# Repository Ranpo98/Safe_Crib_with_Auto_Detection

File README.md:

# Safe Crib With Auto Hazard-Detection

## Project Overview

**Duration**: December 2022 – May 2023

The "Safe Crib With Auto Hazard-Detection" is an innovative project aimed at utilizing technology to enhance the safety of infants while in their cribs. The project focuses on developing a system that employs various sensor arrays to monitor the baby's movements and posture in the crib, alerting caregivers to potential unintentional falls and other hazards. 

## Features and Achievements

- Utilization of various sensor arrays to closely monitor baby's movements and posture within the crib, providing alerts for unintentional falls.
- Independent PCB design, forming the central control hub for the sensor array and a Bluetooth module facilitating data transmission.
- Simulation and testing of PCB conditions with extensive sensor arrays connected, using Kicad and Cadence® Virtuoso®.
- Prototyping and real-situation sensor accuracy testing with the aid of a breadboard and a crib model crafted with machine tools.
- Implementation of Arduino IDE encoder to program the receiving PCB, and store the predetermined method for decoding transmitted bit signals.
- Nominated for a showcase during the Senior Project design and approval stage, securing a full score in the evaluation phase.

## Technologies Used

- Sensor Arrays
- Bluetooth Module
- Kicad
- Cadence® Virtuoso®
- Arduino IDE

## Repository Contents

In this repository, you will find all the files generated throughout the project's progression.

### ⚠️ License & Usage

Please note that unauthorized use of any files or code found within this repository without explicit permission is strictly prohibited.

## Getting Started

To delve deeper into the project details, navigate through the repository. Inside, you will find a rich collection of files, including but not limited to:

- Circuit Designs
- Code Files
- Sensor Calibration Data
- Prototyping Images and Videos

## Conclusion

This project stands as a testament to the fusion of technology and child safety, embodying innovation and dedication.

Thank you for visiting the "Safe Crib With Auto Hazard-Detection" project repository!

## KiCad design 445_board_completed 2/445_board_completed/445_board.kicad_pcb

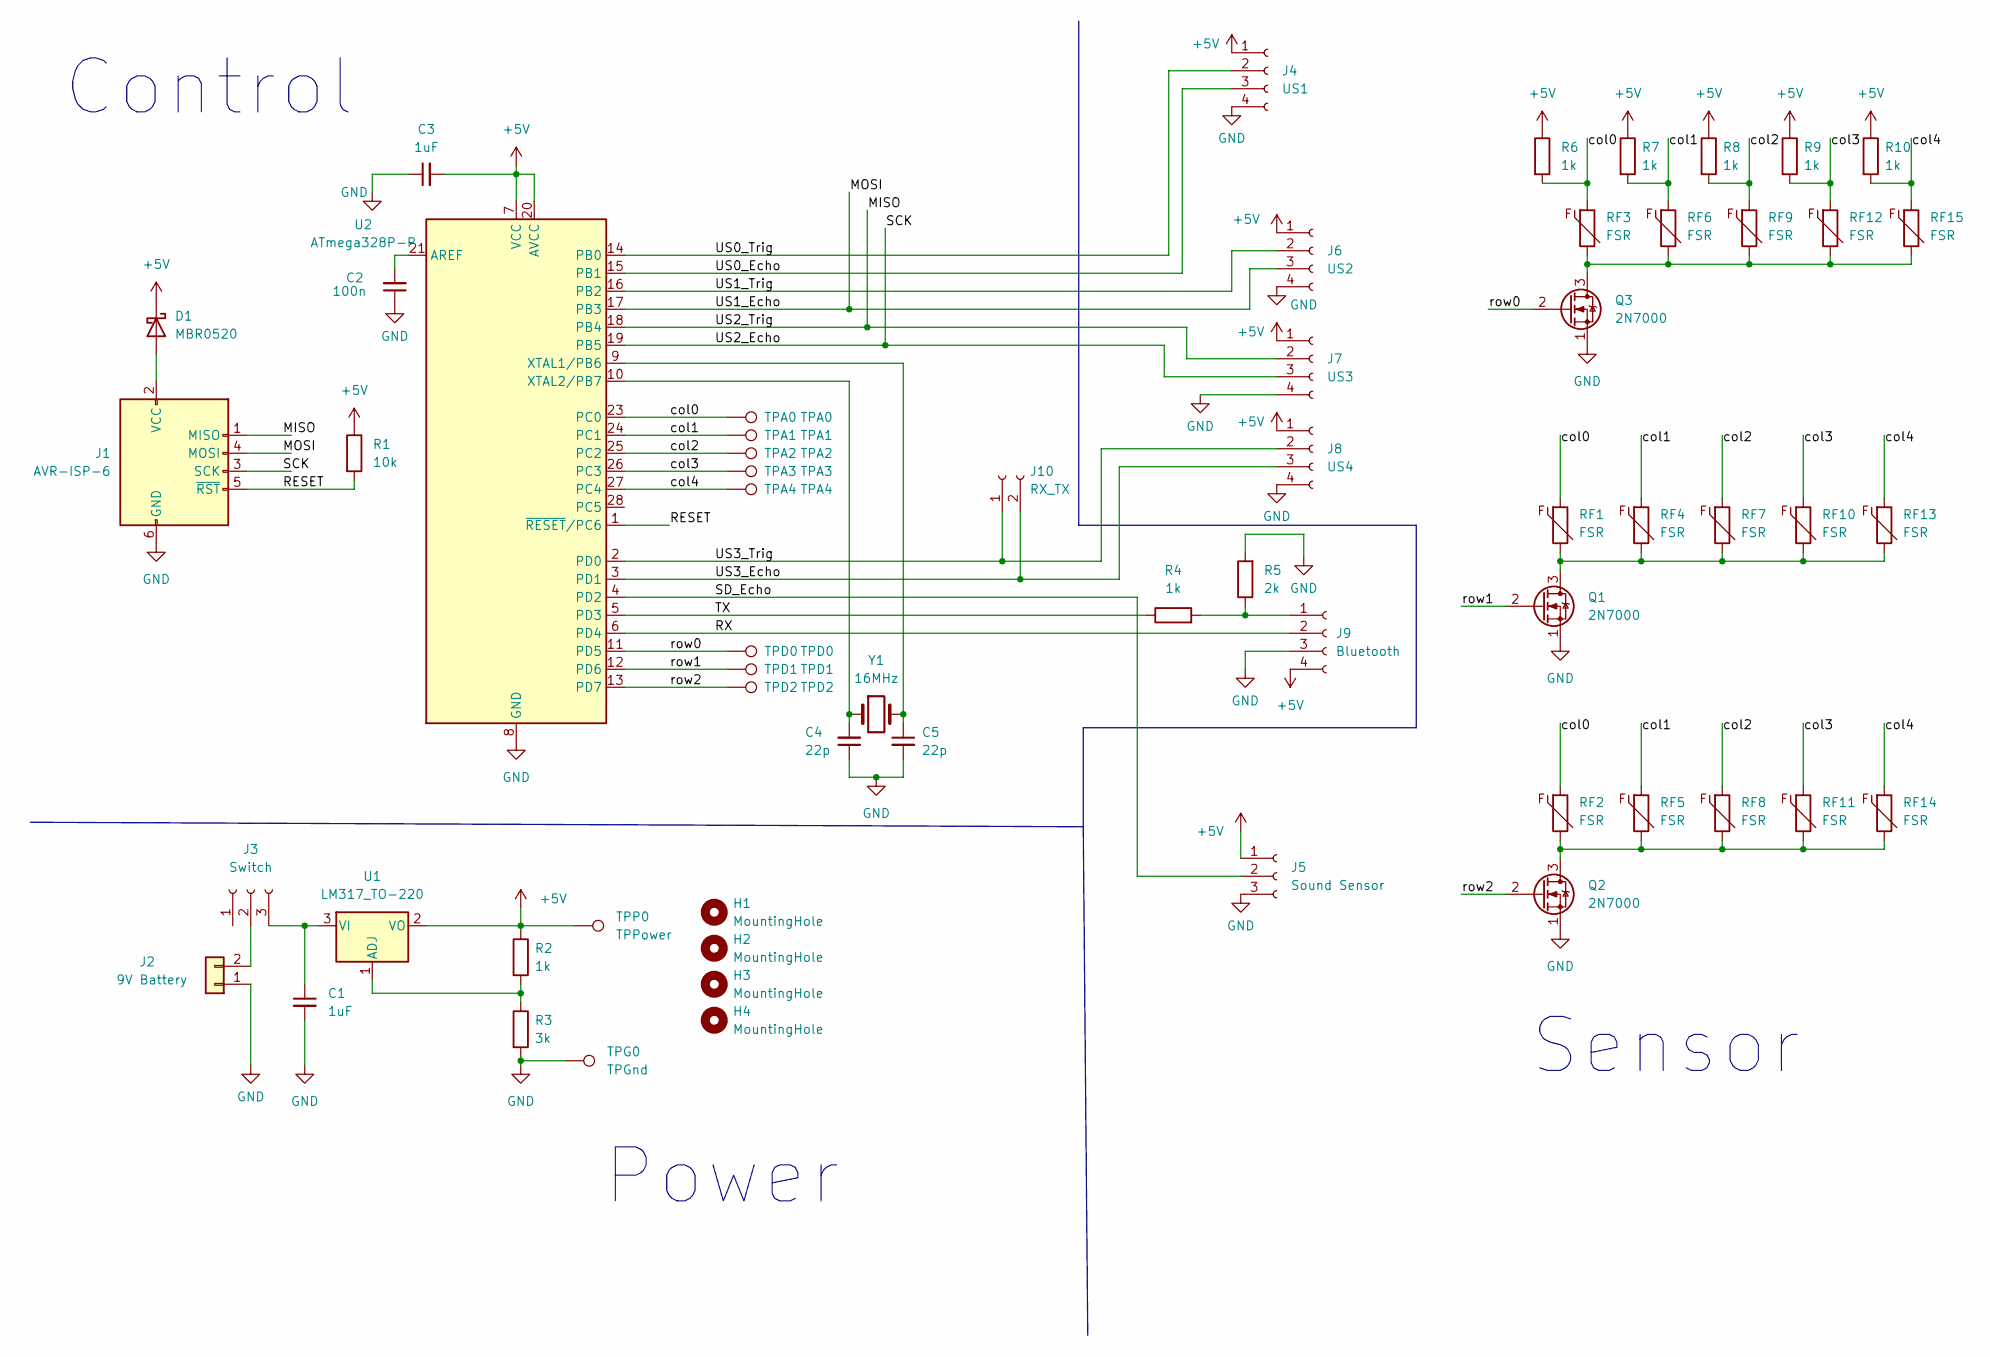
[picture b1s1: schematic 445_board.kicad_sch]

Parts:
C1, C3: 1uF; C_Disc_D7.5mm_W5.0mm_P5.00mm
C2: 100n; C_Disc_D7.5mm_W5.0mm_P5.00mm
C4, C5: 22p; C_Disc_D7.5mm_W5.0mm_P5.00mm
D1: MBR0520; D_SOD-123
H1, H2, H3, H4: MountingHole; MountingHole_3.2mm_M3
J1: AVR-ISP-6; IDC-Header_2x03_P2.54mm_Vertical
J2: 9V Battery; PinSocket_1x02_P2.54mm_Vertical
J3: Switch; PinSocket_1x03_P2.54mm_Vertical
J4: US1; PinSocket_1x04_P2.54mm_Vertical
J5: Sound Sensor; PinSocket_1x03_P2.54mm_Vertical
J6: US2; PinSocket_1x04_P2.54mm_Vertical
J7: US3; PinSocket_1x04_P2.54mm_Vertical
J8: US4; PinSocket_1x04_P2.54mm_Vertical
J9: Bluetooth; PinSocket_1x04_P2.54mm_Vertical
J10: RX_TX; PinSocket_1x02_P2.54mm_Vertical
Q1, Q2, Q3: 2N7000; TO-92_Inline
R1: 10k; R_Axial_DIN0207_L6.3mm_D2.5mm_P10.16mm_Horizontal
R2, R4, R6, R7, R8, R9, R10: 1k; R_Axial_DIN0207_L6.3mm_D2.5mm_P10.16mm_Horizontal
R3: 3k; R_Axial_DIN0207_L6.3mm_D2.5mm_P10.16mm_Horizontal
R5: 2k; R_Axial_DIN0207_L6.3mm_D2.5mm_P10.16mm_Horizontal
RF1, RF2, RF3, RF4, RF5, RF6, RF7, RF8, RF9, RF10, RF11, RF12, RF13, RF14, RF15: FSR; R_Axial_DIN0204_L3.6mm_D1.6mm_P5.08mm_Vertical
TPA0: TPA0; TestPoint_THTPad_2.5x2.5mm_Drill1.2mm
TPA1: TPA1; TestPoint_THTPad_2.5x2.5mm_Drill1.2mm
TPA2: TPA2; TestPoint_THTPad_2.5x2.5mm_Drill1.2mm
TPA3: TPA3; TestPoint_THTPad_2.5x2.5mm_Drill1.2mm
TPA4: TPA4; TestPoint_THTPad_2.5x2.5mm_Drill1.2mm
TPD0: TPD0; TestPoint_THTPad_2.5x2.5mm_Drill1.2mm
TPD1: TPD1; TestPoint_THTPad_2.5x2.5mm_Drill1.2mm
TPD2: TPD2; TestPoint_THTPad_2.5x2.5mm_Drill1.2mm
TPG0: TPGnd; TestPoint_THTPad_3.0x3.0mm_Drill1.5mm
TPP0: TPPower; TestPoint_THTPad_3.0x3.0mm_Drill1.5mm
U1: LM317_TO-220; TO-220-3_Vertical
U2: ATmega328P-P; DIP-28_W7.62mm
Y1: 16MHz; Crystal_HC49-U_Vertical

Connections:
+5V: C3.2, D1.1 (K), J4.1, J5.1, J6.1, J7.1, J8.1, J9.4, R1.1, R2.1, R6.1, R7.1, R8.1, R9.1, R10.1, TPP0.1, U1.2 (VO), U2.7 (VCC), U2.20 (AVCC)
/MISO: J1.1 (MISO), J7.2, U2.18 (PB4)
/MOSI: J1.4 (MOSI), J6.3, U2.17 (PB3)
/RESET: J1.5 (~RST), R1.2, U2.1 (~RESET/PC6)
/RX: J9.2, U2.6 (PD4)
/SCK: J1.3 (SCK), J7.3, U2.19 (PB5)
/SD_Echo: J5.2, U2.4 (PD2)
/TX: R4.1, U2.5 (PD3)
/US0_Echo: J4.3, U2.15 (PB1)
/US0_Trig: J4.2, U2.14 (PB0)
/US1_Trig: J6.2, U2.16 (PB2)
/US3_Echo: J8.3, J10.2, U2.3 (PD1)
/US3_Trig: J8.2, J10.1, U2.2 (PD0)
/col0: R6.2, RF1.1, RF2.1, RF3.1, TPA0.1, U2.23 (PC0)
/col1: R7.2, RF4.1, RF5.1, RF6.1, TPA1.1, U2.24 (PC1)
/col2: R8.2, RF7.1, RF8.1, RF9.1, TPA2.1, U2.25 (PC2)
/col3: R9.2, RF10.1, RF11.1, RF12.1, TPA3.1, U2.26 (PC3)
/col4: R10.2, RF13.1, RF14.1, RF15.1, TPA4.1, U2.27 (PC4)
/row0: Q3.2 (G), TPD0.1, U2.11 (PD5)
/row1: Q1.2 (G), TPD1.1, U2.12 (PD6)
/row2: Q2.2 (G), TPD2.1, U2.13 (PD7)
GND: C1.2, C2.1, C3.1, C4.1, C5.2, J1.6 (GND), J2.1, J4.4, J5.3, J6.4, J7.4, J8.4, J9.3, Q1.1 (S), Q2.1 (S), Q3.1 (S), R3.2, R5.2, TPG0.1, U2.8 (GND), U2.22 (GND)
unnamed: C1.1, J3.3, U1.3 (VI)
unnamed: C2.2, U2.21 (AREF)
unnamed: C4.2, U2.10 (XTAL2/PB7), Y1.1
unnamed: C5.1, U2.9 (XTAL1/PB6), Y1.2
unnamed: D1.2 (A), J1.2 (VCC)
unnamed: J2.2, J3.2
unnamed: J9.1, R4.2, R5.1
unnamed: Q1.3 (D), RF1.2, RF4.2, RF7.2, RF10.2, RF13.2
unnamed: Q2.3 (D), RF2.2, RF5.2, RF8.2, RF11.2, RF14.2
unnamed: Q3.3 (D), RF3.2, RF6.2, RF9.2, RF12.2, RF15.2
unnamed: R2.2, R3.1, U1.1 (ADJ)

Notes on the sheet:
Control
Sensor
Power

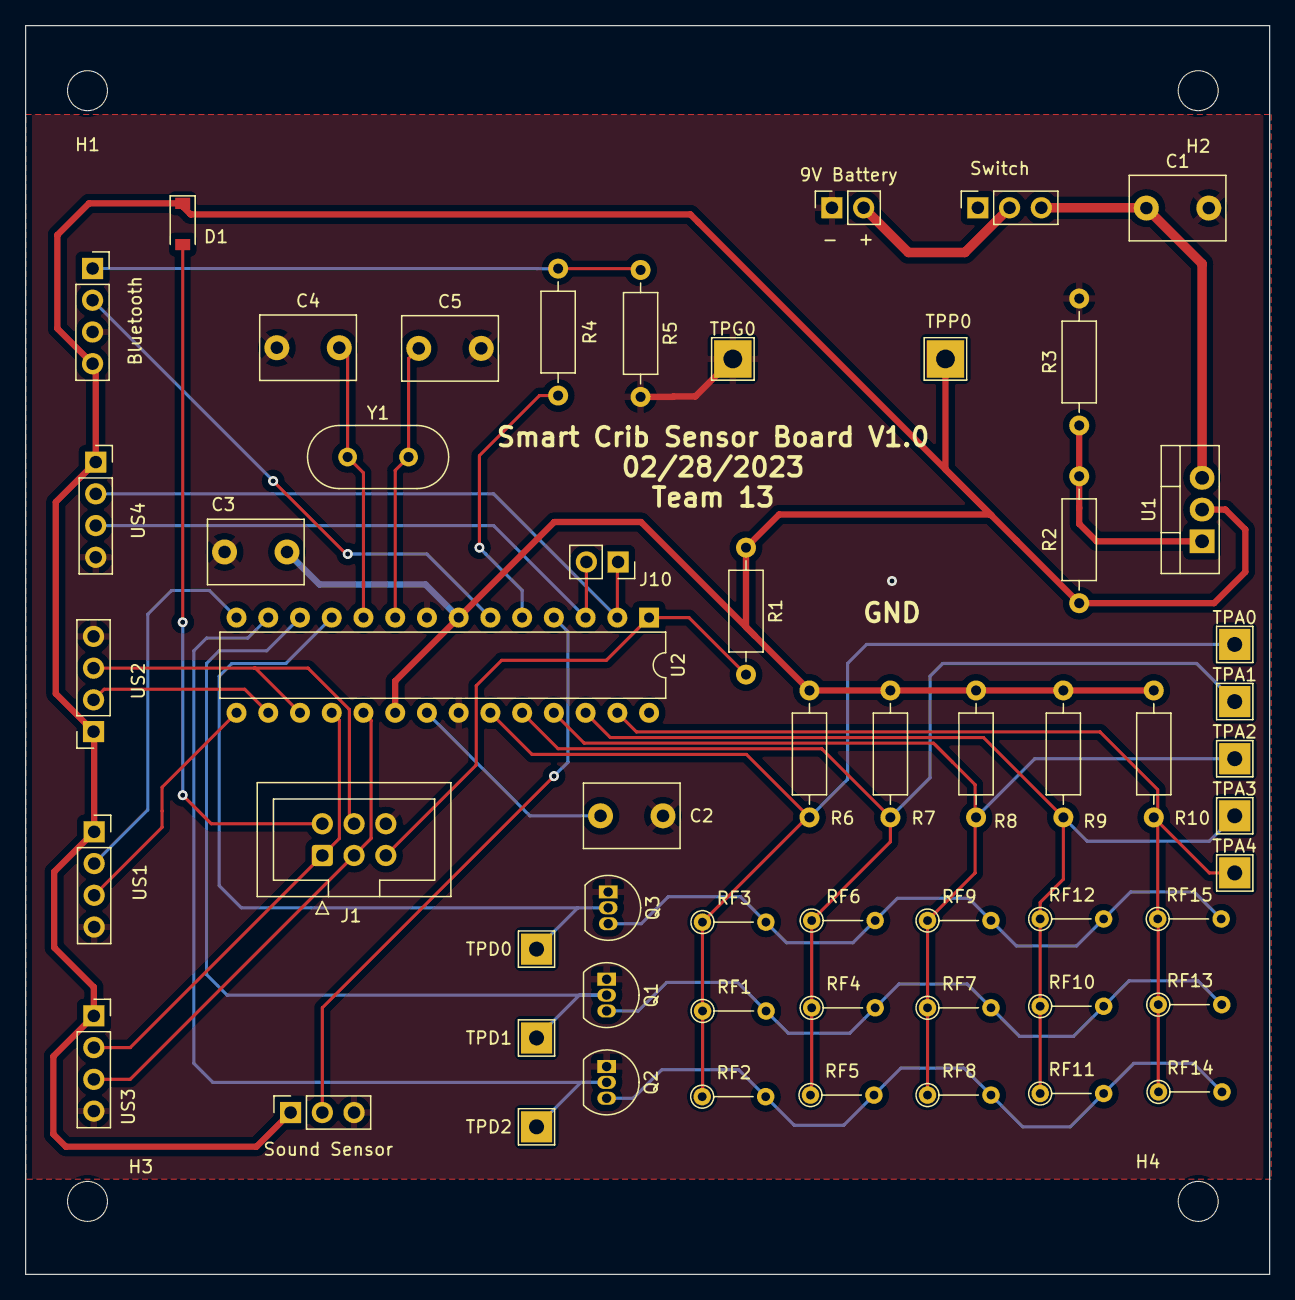
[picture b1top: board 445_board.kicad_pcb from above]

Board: 2 copper layers, 99.6 x 99.9 mm, 61 parts (0 on the bottom side), 33 nets.

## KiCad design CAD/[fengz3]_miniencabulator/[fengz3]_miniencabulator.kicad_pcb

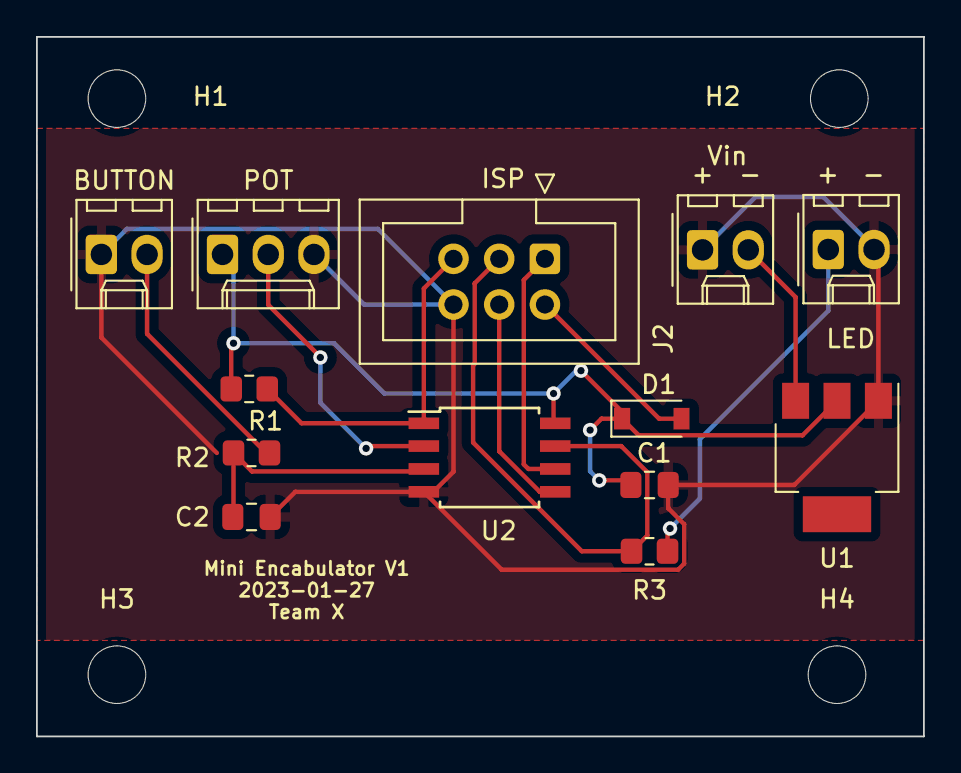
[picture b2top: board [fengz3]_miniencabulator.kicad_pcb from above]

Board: 2 copper layers, 49.3 x 38.9 mm, 17 parts (0 on the bottom side), 12 nets.

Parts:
BUTTON: Button; Molex_KK-254_AE-6410-02A_1x02_P2.54mm_Vertical
C1, C2: 1uF; C_0805_2012Metric_Pad1.18x1.45mm_HandSolder
D1: MBR0520; D_SOD-123
H1, H2, H3, H4: MountingHole; MountingHole_3.2mm_M3
J2: ISP; IDC-Header_2x03_P2.54mm_Vertical
LED: LED; Molex_KK-254_AE-6410-02A_1x02_P2.54mm_Vertical
POT: POT; Molex_KK-254_AE-6410-03A_1x03_P2.54mm_Vertical
R1, R2: 10k; R_0805_2012Metric_Pad1.20x1.40mm_HandSolder
R3: 1k; R_0805_2012Metric_Pad1.20x1.40mm_HandSolder
U1: LM1117-5.0; SOT-223
U2: ATtiny85-20S; SOIC-8W_5.3x5.3mm_P1.27mm
Vin: Vin; Molex_KK-254_AE-6410-02A_1x02_P2.54mm_Vertical

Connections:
+5V: C1.1, D1.1 (K), POT.1, R1.1, U1.2 (VO), U2.8 (VCC)
/BUTTON: C2.1, R2.1, U2.3 (XTAL2/PB4)
/MISO: J2.1 (MISO), U2.6 (PB1)
/MOSI: J2.4 (MOSI), U2.5 (AREF/PB0)
/RST: J2.5 (~RST), R1.2, U2.1 (~RESET/PB5)
/SCK: J2.3 (SCK), R3.2, U2.7 (PB2)
GND: BUTTON.1, C1.2, C2.2, J2.6 (GND), LED.2, POT.3, U1.1 (GND), U2.4 (GND), Vin.1
unnamed: D1.2 (A), J2.2 (VCC)
unnamed: U1.3 (VI), Vin.2
unnamed: LED.1, R3.1
unnamed: BUTTON.2, R2.2
unnamed: POT.2, U2.2 (XTAL1/PB3)

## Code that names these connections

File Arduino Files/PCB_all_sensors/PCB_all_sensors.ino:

const int trigPin0 = PIN_PB0;
const int echoPin0 = PIN_PB1;
const int trigPin1 = PIN_PB2;
const int echoPin1 = PIN_PB3;
const int trigPin2 = PIN_PB4;
const int echoPin2 = PIN_PB5;
const int trigPin3 = PIN_PD0;
const int echoPin3 = PIN_PD1;
const int PIN_ANALOG_IN = PIN_PC5;
const int PIN_GATE_IN = PIN_PD2;
const int trigPin0_p = PIN_PD5;
const int trigPin1_p = PIN_PD6;
const int trigPin2_p = PIN_PD7;
const int sensorPin0 = PIN_PC0;
const int sensorPin1 = PIN_PC1;
const int sensorPin2 = PIN_PC2;
const int sensorPin3 = PIN_PC3;
const int sensorPin4 = PIN_PC4;

const int BT_RX = PIN_PD3;
const int BT_TX = PIN_PD4;

int BTdelay = 50;
byte newstates = 0b00000000;
unsigned long lasttime = 0;
long duration, distance, Distance0, Distance1, Distance2, Distance3;
int ana_val = 0;
int gate_val = 0;
int n = 0;
int ss_sample_lasttime = 0;
int ss_sample_delay = 400;
int ss_alarm_lasttime = 0;
int ss_alarm_delay = 2000;
int ss_threshold = 150;
bool ss_alarm_remain = false;
bool hasrun = false;
int count = 0;
int ps_delay=10;
int ps_threshold = 1018;
unsigned long last_ps_time = 0;
int displacement = 0;
int dig_val[4] = {0,0,0,0};


int a[3][5] = {0};
int b[3][5] = {0};


#include <SoftwareSerial.h>
SoftwareSerial hc05(BT_TX, BT_RX);

void setup() {
  // put your setup code here, to run once:
  pinMode(trigPin0, OUTPUT);
  pinMode(echoPin0, INPUT);
  pinMode(trigPin1, OUTPUT);
  pinMode(echoPin1, INPUT);
  pinMode(trigPin2, OUTPUT);
  pinMode(echoPin2, INPUT);
  pinMode(trigPin3, OUTPUT);
  pinMode(echoPin3, INPUT);
  pinMode(PIN_ANALOG_IN, INPUT);
  pinMode(trigPin0_p, OUTPUT);
  pinMode(trigPin1_p, OUTPUT);
  pinMode(trigPin2_p, OUTPUT);
  hc05.begin(9600);
}

void loop() {
  byte states = 0b00000000;
  //Ultrasonic Sensor
  SonarSensor(trigPin0, echoPin0); //need 65
  Distance0 = distance;
  SonarSensor(trigPin1, echoPin1);  //need 65
  Distance1 = distance;
  SonarSensor(trigPin2, echoPin2);
  Distance2 = distance;  
  SonarSensor(trigPin3, echoPin3);
  Distance3 = distance;

  int arr[4] = {Distance0, Distance1, Distance2, Distance3};
  // int arr[1] = {Distance1};
  //int arr[2] = {Distance1, Distance3};
  //int arr[3] = {Distance0, Distance1, Distance3};

  for(int i = 0; i <= 3; i++){
    if(arr[i] <= 65){
      bitSet(states, 0);//set the 1st bit
      break;
    }
  }

  //Sound Sensor
  //analog version
  // ana_val = analogRead(PIN_ANALOG_IN);

  // if(ana_val >= 150){
  //   bitSet(states, 1);//set the 2nd bit
  // }
  // gate_val = digitalRead(PIN_GATE_IN);
  // if(gate_val == 1){
  //   bitSet(states, 1);//set the 2nd bit
  // }
  //-------------------------------------------------------------------
  // complicated version
  if(dig_val[0] == 1 && dig_val[1] == 1 && dig_val[2] == 1 && dig_val[3] == 1){
    bitSet(states, 1);
    //ss_alarm_remain = true;
    ss_alarm_lasttime = millis();
  }

  if(millis() >= ss_sample_lasttime + ss_sample_delay){
    for (int i = 0; i < 3; ++i) {
      dig_val[i] = dig_val[i + 1];
    }
    dig_val[3] = digitalRead(PIN_GATE_IN);
    ss_sample_lasttime = millis();
    // n++;
  }
  //-------------------------------------------------------------------

  // //  else {
  // //   ss_alarm_remain = false;
  // // }

  // if(n == 4){
  //   n = 0;
  // }  

  // if(millis() <= ss_alarm_lasttime + ss_alarm_delay){
  //   if (ss_alarm_remain == true) {
  //     bitSet(states, 1);
  //   }
  // }
  
  //Pressure Sensor
  if(hasrun == false){
    ReadPressureSensor();
    for(int i = 0; i <= 2; i++){
      for(int j = 0; j<= 4; j++){
        if(a[i][j] <= ps_threshold){
          a[i][j] = 1;
        }else{
          a[i][j] = 0;
        }
        b[i][j] = a[i][j];
        a[i][j] = 0;
      }
    }

    hasrun = true;  
  }

  for(int i = 0; i <= 9; i++){
    ReadPressureSensor(); 
  }  

for(int i = 0; i <= 2; i++){
    for(int j = 0; j<= 4; j++){
      a[i][j] = a[i][j] / 10;
      if(a[i][j] <= ps_threshold){
          a[i][j] = 1;
        }else{
          a[i][j] = 0;
        }
      //calculate the number of position change
      displacement = a[i][j]-b[i][j];
      if(displacement != 0){
        count++;
      }
    }
  }  

  if(count >= 1){
    bitSet(states, 2);
  }

  displacement = 0;
  count = 0;
  for(int i = 0; i <= 2; i++){
    for(int j = 0; j <= 4; j++){
      b[i][j] = a[i][j];
      a[i][j] = 0;
    }
  }

  if(millis() < lasttime + BTdelay){
    newstates = newstates | states;
  } else {
    hc05.write(newstates);
    newstates = newstates & 0;
    lasttime = millis();
  }
}

void SonarSensor(int trigPin, int echoPin){
  digitalWrite(trigPin, LOW);
  delayMicroseconds(2);
  digitalWrite(trigPin, HIGH);
  delayMicroseconds(10);
  digitalWrite(trigPin, LOW);
  duration = pulseIn(echoPin, HIGH);
  distance = (duration/2) / 29.1;
}
void ReadPressureSensor(){
  digitalWrite(trigPin0_p, HIGH);
  digitalWrite(trigPin1_p, LOW);
  digitalWrite(trigPin2_p, LOW);
  
  delayMicroseconds(ps_delay);      
  a[0][0]=a[0][0]+analogRead(sensorPin0);
  a[0][1]=a[0][1]+analogRead(sensorPin1);
  a[0][2]=a[0][2]+analogRead(sensorPin2);
  a[0][3]=a[0][3]+analogRead(sensorPin3);
  a[0][4]=a[0][4]+analogRead(sensorPin4);


  //second 1*5
  digitalWrite(trigPin0_p, LOW);
  digitalWrite(trigPin1_p, HIGH);
  digitalWrite(trigPin2_p, LOW);

  delayMicroseconds(ps_delay);    
  a[1][0]=a[1][0]+analogRead(sensorPin0);
  a[1][1]=a[1][1]+analogRead(sensorPin1);
  a[1][2]=a[1][2]+analogRead(sensorPin2);
  a[1][3]=a[1][3]+analogRead(sensorPin3);
  a[1][4]=a[1][4]+analogRead(sensorPin4);

  //third 1*5
  digitalWrite(trigPin0_p, LOW);
  digitalWrite(trigPin1_p, LOW);
  digitalWrite(trigPin2_p, HIGH);
  
  delayMicroseconds(ps_delay);    
  
  a[2][0]=a[2][0]+analogRead(sensorPin0);
  a[2][1]=a[2][1]+analogRead(sensorPin1);
  a[2][2]=a[2][2]+analogRead(sensorPin2);
  a[2][3]=a[2][3]+analogRead(sensorPin3);
  a[2][4]=a[2][4]+analogRead(sensorPin4);

}

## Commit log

2023-09-09 09/09
